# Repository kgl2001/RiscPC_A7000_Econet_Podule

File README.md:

# Introduction

This Econet Podule allows you to add Econet to your Acorn RISC PC or A7000.

The Podule has four main hardware sections:
  
* [Flash & Address Decoding](#flash--address-decoding)
* [Econet Module](#econet-module)
* Econet Clock
  - [WFF Implementation](#econet-clock---wff-implementation)
  - [Pico Implementation](#econet-clock---pico-implementation)
* [Termination](#onboard-termination)

By adding the Clock / Termination to the PCB, and by populating all four DIN5 sockets, the Acorn RISC PC or A7000 can act as an 'all in one' File Server solution when used along with Acorns Level 4 File Server software. No external clock, termination, or network infrastructure required. Just plug your client Econet enabled machine to one of the four DIN5 sockets on the rear of the board.

Some general notes about the different hardware sections, and RISC OS configuration, are provided below:

## Flash & Address Decoding
The Flash & Address Decoding hardware must be installed in all cases. Flash memory ICs SST39SF010, SST39SF020 or SST39SF040 (or equivalent) can be used with this module. Flash IC contents, `eco_flash` are included in a compressed .zip file within this repo. The unzipped `eco_flash` code should be written to the flash IC using a suitable programmer.

## Econet Module
The Podule PCB is provided with a 5 and 17 pin header, so you can plug in an ADF-10 or AEH-52 (or equivalent) module into the podule, instead of having to solder on all the Econet module components.

Econet Data Tx, Data Rx and Clock LEDs are present on the PCB. However, these will only work if you plan to add the other Econet components directly to the PCB. They won't work if you plan to use an ADF-10 or AEH-52 module.

If installing the Econet components directly onto the PCB, then one of the two channels of the line driver IC7 will be available for use by the onboard Econet clock circuit. If not installing the Econet clock circuit, it is still necessary to install resistor R31. This will disable the clock channel on the line driver, preventing it from interfering with any external clock.

## Econet Clock - WFF Implementation
The Econet clock is based on an original design by Simon Inns. Details can be found [here](https://www.waitingforfriday.com/?p=19).

The clock circuit has been modified slightly, so instead of driving the external hardware directly from the PIC, it is driven by the second channel on the Econet line driver that is otherwise spare.

If using an ADF-10 or AEH-52 module, instead of soldering the Econet parts directly onto the PCB, the second channel is unavailable to the Econet clock hardware. In this instance, if planning to install the onboard Econet clock circuit, it will be necessary to also install IC7 and resistor R25. The purpose of R25 is to disable the unused data channel on the line driver, preventing it from interfering with the network.

When the clock hardware is installed, channel 4 of DIP switch, SW1, can be used to enable or disable the clock hardware. When open circuit, the clock hardware is disabled. When short circuit, the clock hardware is enabled.

The PIC has two clock output signals that can be used to drive the external hardware directly, bypassing the clock channel of line driver IC7 completely. Jumper bank J6 can be used to connect the two clock signals from the PIC directly to external hardware. This is not a recommended configuration. However, if using these jumpers, then the clock channel of IC7 (if fitted) must be disabled.

Jumper JP5 is used to select which of the two clock output signals from the PIC is used to drive the clock channel of line driver IC7.

## Econet Clock - Pico Implementation
Provision has been made to connect a Pico based clock via a 2x20 pin header. This was primarily designed to accept a Pico board that was originally developed for other purposes. See [here](https://stardot.org.uk/forums/viewtopic.php?t=24932).

Like the WFF implementation, this solution also relies on the second channel of line driver IC7, so it needs to be fitted, along with R31, for this clock to work.

When this Pico clock module is plugged in, the second channel of line driver IC7 is enabled automatically (via Pico module Pin 20, which is tied to GND). It can only be disabled again by unplugging the Pico clock module. This would need to be done if using an external clock.

## Onboard Termination
An Econet network needs to be terminated to operate reliably. On larger networks this is typically done at the far ends of the network. Often, on these larger networks, an SJ Research clock is used. These clocks have a special circuit that allows special 'phantom powered' terminators to be used at the far ends. These special terminators are not compatible with the WFF clock or Pico clock used on this board. Instead, if using the onboard clock, then the onboard powered termination should be enabled. Jumper bank J3 is used to enable of disable the termination. Remove the jumpers to disable the termination.

## Configuring RISC OS
Please refer to [this](https://stardot.org.uk/forums/viewtopic.php?p=409582#p409582) post which provides guidance on configuring the RISC PC / A7000.

## Author

The RISC PC / A7000 Econet podule is developed and maintained by Ken Lowe.
    
## Hardware License (Creative Commons BY-SA 4.0)

Please see the following link for details: https://creativecommons.org/licenses/by-sa/4.0/

You are free to:

Share - copy and redistribute the material in any medium or format
Adapt - remix, transform, and build upon the material
for any purpose, even commercially.

This license is acceptable for Free Cultural Works.

The licensor cannot revoke these freedoms as long as you follow the license terms.

Under the following terms:

Attribution - You must give appropriate credit, provide a link to the license, and indicate if changes were made. You may do so in any reasonable manner, but not in any way that suggests the licensor endorses you or your use.

ShareAlike - If you remix, transform, or build upon the material, you must distribute your contributions under the same license as the original.

No additional restrictions - You may not apply legal terms or technological measures that legally restrict others from doing anything the license permits.

## Schematic and 3D Render
Econet Podule - Schematic:

Econet Podule - 3D Render:

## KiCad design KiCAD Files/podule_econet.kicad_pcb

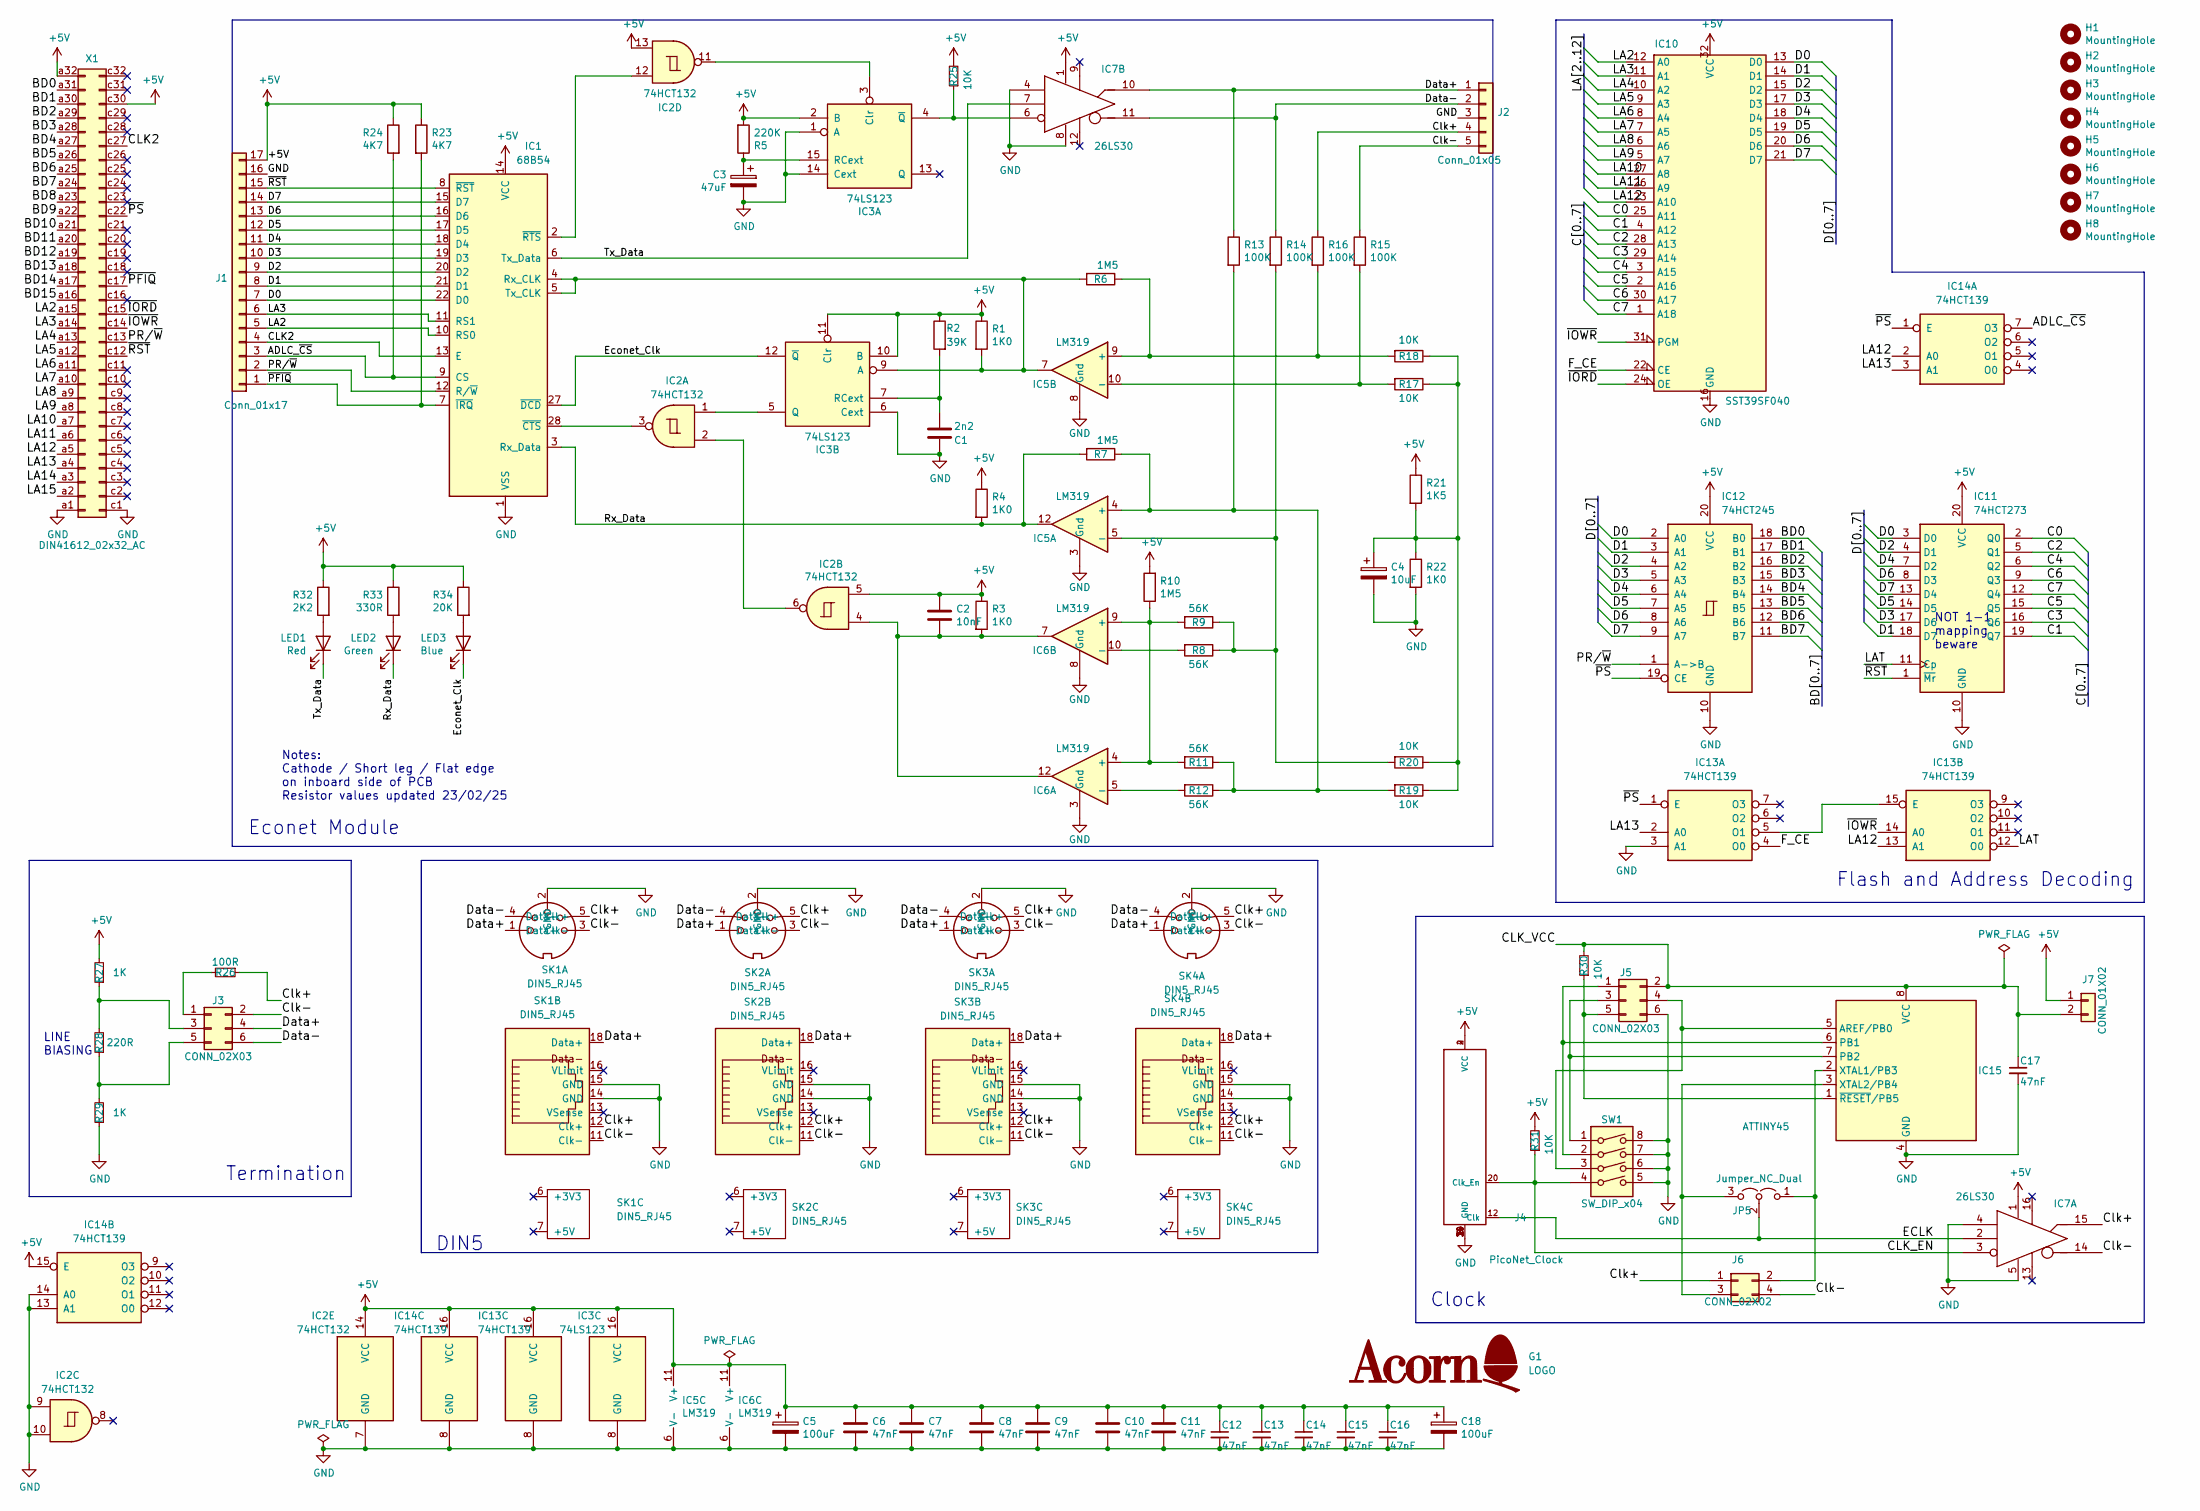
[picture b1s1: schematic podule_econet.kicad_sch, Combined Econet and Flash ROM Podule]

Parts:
C1: 2n2; C_Disc_D4.3mm_W1.9mm_P5.00_P2.54mm
C2: 10nF; C_Disc_D4.3mm_W1.9mm_P5.00_P2.54mm
C3: 47uF; CP_Radial_Tantal_D6.0mm_P2.50mm
C4: 10uF; CP_Radial_D5.0mm_P2.00mm
C5, C18: 100uF; CP_Radial_D5.0mm_P2.00mm
C6, C7, C8, C9, C10, C11, C12, C13, C14, C15, C16, C17: 47nF; C_Disc_D4.3mm_W1.9mm_P5.00mm
G1: LOGO; AcornLogo2
H1, H2, H3, H4, H7, H8: MountingHole; MountingHole_2.7mm
H5, H6: MountingHole; MountingHole_4mm
IC1: 68B54; DIP-28_W15.24mm
IC2: 74HCT132; DIP-14_W7.62mm
IC3: 74LS123; DIP-16_W7.62mm
IC5, IC6: LM319; DIP-14_W7.62mm
IC7: 26LS30; DIP-16_W7.62mm
IC10: SST39SF040; DIP-32_W15.24mm
IC11: 74HCT273; DIP-20_W7.62mm
IC12: 74HCT245; DIP-20_W7.62mm
IC13, IC14: 74HCT139; DIP-16_W7.62mm
IC15: ATTINY45; DIP-8_W7.62mm
J1: Conn_01x17; PinSocket_1x17_P2.54mm_Vertical
J2: Conn_01x05; PinSocket_1x05_P2.54mm_Vertical
J3, J5: CONN_02X03; PinHeader_2x03_P2.54mm_Vertical
J4: PicoNet_Clock; PicoNetClock
J6: CONN_02X02; PinHeader_2x02_P2.54mm_Vertical
J7: CONN_01X02; PinHeader_1x02_P2.54mm_Vertical
JP5: Jumper_NC_Dual; PinHeader_1x03_P2.54mm_Vertical
LED1: Red; LED_D3.0mm
LED2: Green; LED_D3.0mm
LED3: Blue; LED_D3.0mm
R1, R3, R4, R22: 1K0; R_Axial_DIN0207_L6.3mm_D2.5mm_P10.16mm_Horizontal
R2: 39K; R_Axial_DIN0207_L6.3mm_D2.5mm_P10.16mm_Horizontal
R5: 220K; R_Axial_DIN0207_L6.3mm_D2.5mm_P10.16mm_Horizontal
R6, R7, R10: 1M5; R_Axial_DIN0207_L6.3mm_D2.5mm_P10.16mm_Horizontal
R8, R9, R11, R12: 56K; R_Axial_DIN0207_L6.3mm_D2.5mm_P10.16mm_Horizontal
R13, R14, R15, R16: 100K; R_Axial_DIN0207_L6.3mm_D2.5mm_P10.16mm_Horizontal
R17, R18, R19, R20, R25, R30, R31: 10K; R_Axial_DIN0207_L6.3mm_D2.5mm_P10.16mm_Horizontal
R21: 1K5; R_Axial_DIN0207_L6.3mm_D2.5mm_P10.16mm_Horizontal
R23, R24: 4K7; R_Axial_DIN0207_L6.3mm_D2.5mm_P10.16mm_Horizontal
R26: 100R; R_Axial_DIN0207_L6.3mm_D2.5mm_P10.16mm_Horizontal
R27, R29: 1K; R_Axial_DIN0207_L6.3mm_D2.5mm_P10.16mm_Horizontal
R28: 220R; R_Axial_DIN0207_L6.3mm_D2.5mm_P10.16mm_Horizontal
R32: 2K2; R_Axial_DIN0207_L6.3mm_D2.5mm_P10.16mm_Horizontal
R33: 330R; R_Axial_DIN0207_L6.3mm_D2.5mm_P10.16mm_Horizontal
R34: 20K; R_Axial_DIN0207_L6.3mm_D2.5mm_P10.16mm_Horizontal
SK1, SK2, SK3, SK4: DIN5_RJ45; CombinedDIN5RJ45PinHeader90Deg
SW1: SW_DIP_x04; SW_DIP_SPSTx04_Slide_9.78x12.34mm_W7.62mm_P2.54mm
X1: DIN41612_02x32_AC; DIN41612_C_2x32_Male_Horizontal_THT

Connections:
+5V: C2.1, C5.1, C6.1, C7.1, C8.1, C9.1, C10.1, C11.1, C12.1, C13.1, C14.1, C15.1, C16.1, C18.1, IC1.14 (VCC), IC2.5, IC2.13, IC2.14 (VCC), IC3.2 (B), IC3.10 (B), IC3.11 (Clr), IC3.16 (VCC), IC5.11 (V+), IC6.11 (V+), IC7.1 (VCC), IC10.32 (VCC), IC11.20 (VCC), IC12.20 (VCC), IC13.16 (VCC), IC14.15 (E), IC14.16 (VCC), J1.17, J4.2 (VCC), J4.4 (VCC), J7.1, R1.1, R2.1, R3.1, R4.1, R5.2, R10.2, R21.1, R23.1, R24.1, R25.2, R27.2, R31.2, R32.1, R33.1, R34.1, X1.a32, X1.c30
/ADLC_~CS: IC1.9 (CS), IC14.7 (O3), J1.3, R24.2
/BD0: IC12.18 (B0), X1.a31
/BD1: IC12.17 (B1), X1.a30
/BD2: IC12.16 (B2), X1.a29
/BD3: IC12.15 (B3), X1.a28
/BD4: IC12.14 (B4), X1.a27
/BD5: IC12.13 (B5), X1.a26
/BD6: IC12.12 (B6), X1.a25
/BD7: IC12.11 (B7), X1.a24
/BD8: X1.a23
/BD9: X1.a22
/BD10: X1.a21
/BD11: X1.a20
/BD12: X1.a19
/BD13: X1.a18
/BD14: X1.a17
/BD15: X1.a16
/C0: IC10.25 (A11), IC11.2 (Q0)
/C1: IC10.4 (A12), IC11.19 (Q7)
/C2: IC10.28 (A13), IC11.5 (Q1)
/C3: IC10.29 (A14), IC11.16 (Q6)
/C4: IC10.3 (A15), IC11.6 (Q2)
/C5: IC10.2 (A16), IC11.15 (Q5)
/C6: IC10.30 (A17), IC11.9 (Q3)
/C7: IC10.1 (A18), IC11.12 (Q4)
/CLK2: IC1.13 (E), J1.4, X1.c27
/CLK_EN: IC7.3, J4.20 (Clk_En), R31.1, SW1.4
/CLK_VCC: C17.1, IC15.8 (VCC), J5.2, J7.2, R30.2
/Clk+: IC7.15 (OUT+), J2.4, J6.1, R16.1, R26.1, SK1.5 (Clk+), SK1.12 (Clk+), SK2.5 (Clk+), SK2.12 (Clk+), SK3.5 (Clk+), SK3.12 (Clk+), SK4.5 (Clk+), SK4.12 (Clk+)
/Clk-: IC7.14 (OUT-), J2.5, J3.2, J6.4, R15.1, SK1.3 (Clk-), SK1.11 (Clk-), SK2.3 (Clk-), SK2.11 (Clk-), SK3.3 (Clk-), SK3.11 (Clk-), SK4.3 (Clk-), SK4.11 (Clk-)
/D0: IC1.22 (D0), IC10.13 (D0), IC11.3 (D0), IC12.2 (A0), J1.7
/D1: IC1.21 (D1), IC10.14 (D1), IC11.18 (D7), IC12.3 (A1), J1.8
/D2: IC1.20 (D2), IC10.15 (D2), IC11.4 (D1), IC12.4 (A2), J1.9
/D3: IC1.19 (D3), IC10.17 (D3), IC11.17 (D6), IC12.5 (A3), J1.10
/D4: IC1.18 (D4), IC10.18 (D4), IC11.7 (D2), IC12.6 (A4), J1.11
/D5: IC1.17 (D5), IC10.19 (D5), IC11.14 (D5), IC12.7 (A5), J1.12
/D6: IC1.16 (D6), IC10.20 (D6), IC11.8 (D3), IC12.8 (A6), J1.13
/D7: IC1.15 (D7), IC10.21 (D7), IC11.13 (D4), IC12.9 (A7), J1.14
/Data+: IC7.10 (OUT+), J2.1, J3.4, R13.1, SK1.1 (Data+), SK1.18 (Data+), SK2.1 (Data+), SK2.18 (Data+), SK3.1 (Data+), SK3.18 (Data+), SK4.1 (Data+), SK4.18 (Data+)
/Data-: IC7.11 (OUT-), J2.2, J3.6, R14.1, SK1.4 (Data-), SK2.4 (Data-), SK3.4 (Data-), SK4.4 (Data-)
/ECLK: IC7.2 (Enable), J4.12 (Clk), JP5.2 (C)
/Econet_Clk: IC1.27 (~DCD), IC3.12 (~Q), LED3.1 (K)
/F_CE: IC10.22 (CE), IC13.4 (O0)
/LA2: IC1.10 (RS0), IC10.12 (A0), J1.5, X1.a15
/LA3: IC1.11 (RS1), IC10.11 (A1), J1.6, X1.a14
/LA4: IC10.10 (A2), X1.a13
/LA5: IC10.9 (A3), X1.a12
/LA6: IC10.8 (A4), X1.a11
/LA7: IC10.7 (A5), X1.a10
/LA8: IC10.6 (A6), X1.a9
/LA9: IC10.5 (A7), X1.a8
/LA10: IC10.27 (A8), X1.a7
/LA11: IC10.26 (A9), X1.a6
/LA12: IC10.23 (A10), IC13.13 (A1), IC14.2 (A0), X1.a5
/LA13: IC13.2 (A0), IC14.3 (A1), X1.a4
/LA14: X1.a3
/LA15: X1.a2
/LAT: IC11.11 (Cp), IC13.12 (O0)
/Rx_Data: IC1.3 (Rx_Data), IC5.12, LED2.1 (K), R4.2, R7.2
/Tx_Data: IC1.6 (Tx_Data), IC7.7 (Enable), LED1.1 (K)
/~IORD: IC10.24 (OE), X1.c15
/~IOWR: IC10.31 (PGM), IC13.14 (A0), X1.c14
/~PFIQ: IC1.7 (~IRQ), J1.1, R23.2, X1.c17
/~PS: IC12.19 (CE), IC13.1 (E), IC14.1 (E), X1.c22
/~RST: IC1.8 (~RST), IC11.1 (~Mr), J1.15, X1.c12
GND: C1.1, C3.2, C4.2, C5.2, C6.2, C7.2, C8.2, C9.2, C10.2, C11.2, C12.2, C13.2, C14.2, C15.2, C16.2, C17.2, C18.2, IC1.1 (VSS), IC2.7 (GND), IC2.9, IC2.10, IC3.1 (A), IC3.6 (Cext), IC3.8 (GND), IC3.14 (Cext), IC5.3 (Gnd), IC5.6 (V-), IC5.8 (Gnd), IC6.3 (Gnd), IC6.6 (V-), IC6.8 (Gnd), IC7.4 (Mode), IC7.5 (GND), IC7.8 (GND), IC10.16 (GND), IC11.10 (GND), IC12.10 (GND), IC13.3 (A1), IC13.8 (GND), IC14.8 (GND), IC14.13 (A1), IC14.14 (A0), IC15.4 (GND), J1.16, J2.3, J4.6 (GND), J4.9 (GND), J4.14 (GND), J4.25 (GND), J4.30 (GND), J4.34 (GND), J4.39 (GND), J5.6, R22.2, R29.1, SK1.2 (GND), SK1.14 (GND), SK1.15 (GND), SK2.2 (GND), SK2.14 (GND), SK2.15 (GND), SK3.2 (GND), SK3.14 (GND), SK3.15 (GND), SK4.2 (GND), SK4.14 (GND), SK4.15 (GND), SW1.5, SW1.6, SW1.7, SW1.8, X1.a1, X1.c1
unnamed: C2.2, IC2.4, IC6.7, IC6.12, R3.2
unnamed: C4.1, R17.1, R18.1, R19.1, R20.1, R21.2, R22.1
unnamed: IC1.4 (Rx_CLK), IC1.5 (Tx_CLK), IC3.9 (A), IC5.7, R1.2, R6.2
unnamed: IC1.28 (~CTS), IC2.3
unnamed: IC1.2 (~RTS), IC2.12
unnamed: IC2.2, IC2.6
unnamed: IC2.11, IC3.3 (Clr)
unnamed: C3.1, IC3.15 (RCext), R5.1
unnamed: IC3.4 (~Q), IC7.6, R25.1
unnamed: IC2.1, IC3.5 (Q)
unnamed: C1.2, IC3.7 (RCext), R2.2
unnamed: IC5.4 (+), R7.1, R11.1, R12.1, R13.2, R19.2
unnamed: IC5.5 (-), R8.1, R9.1, R14.2, R20.2
unnamed: IC5.9 (+), R6.1, R16.2, R18.2
unnamed: IC5.10 (-), R15.2, R17.2
unnamed: IC6.4 (+), IC6.9 (+), R9.2, R10.1, R11.2
unnamed: IC6.5 (-), R12.2
unnamed: IC6.10 (-), R8.2
unnamed: IC13.5 (O1), IC13.15 (E)
unnamed: IC15.5 (AREF/PB0), J5.4, SW1.3
unnamed: IC15.6 (PB1), J5.1, SW1.2
unnamed: IC15.7 (PB2), J5.3, SW1.1
unnamed: IC15.2 (XTAL1/PB3), J6.2, JP5.1 (A)
unnamed: IC15.3 (XTAL2/PB4), J6.3, JP5.3 (B)
unnamed: IC15.1 (~RESET/PB5), J5.5, R30.1
unnamed: J3.1, R26.2
unnamed: J3.3, R27.1, R28.2
unnamed: J3.5, R28.1, R29.2
unnamed: LED1.2 (A), R32.2
unnamed: LED2.2 (A), R33.2
unnamed: LED3.2 (A), R34.2

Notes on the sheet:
Clock
Termination
NOT 1-1 mapping beware
LINE BIASING
DIN5
Flash and Address Decoding
Econet Module
Notes: Cathode / Short leg / Flat edge on inboard side of PCB Resistor values updated 23/02/25

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
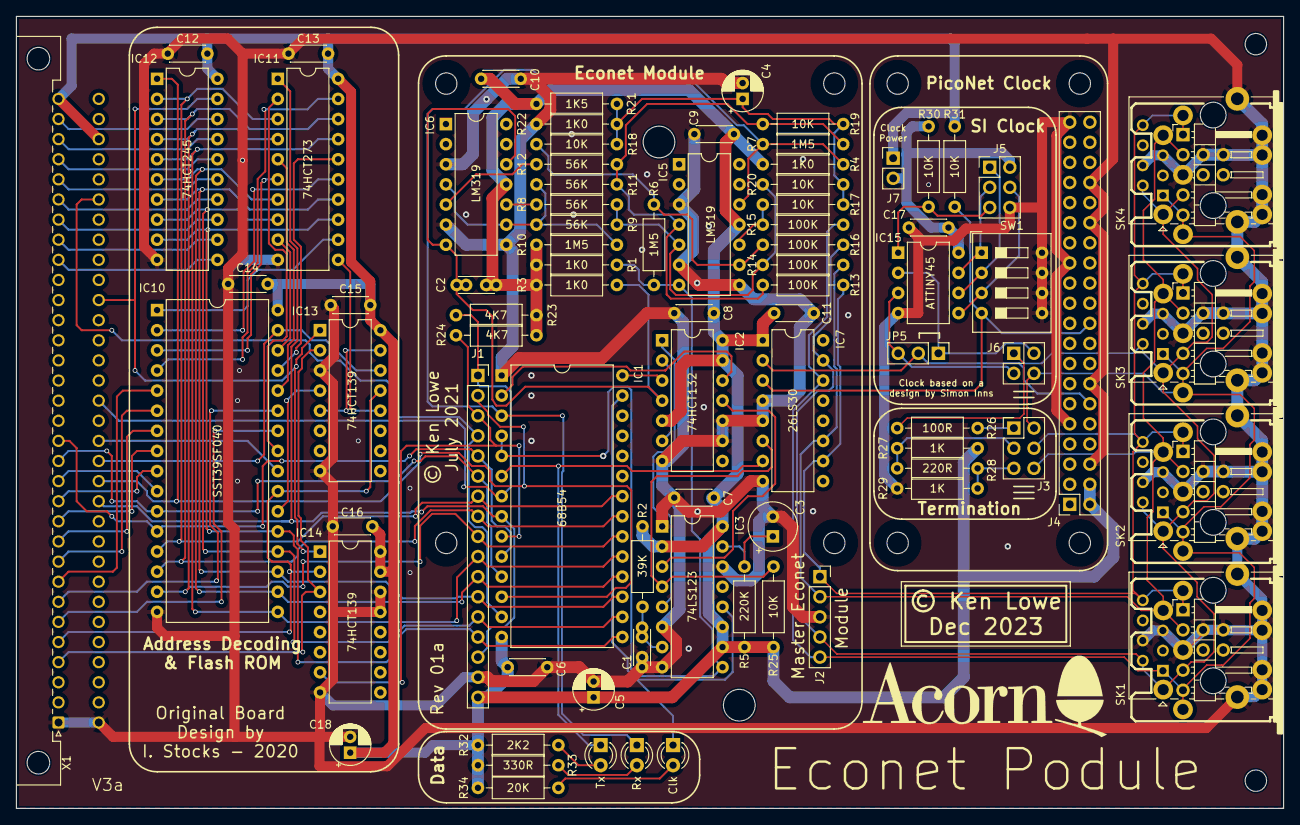
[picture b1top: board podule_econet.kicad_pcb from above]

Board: 2 copper layers, 160.0 x 100.0 mm, 90 parts (0 on the bottom side), 89 nets.

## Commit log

2024-05-24 Create README.md
    Added Schematic and 3D render
2025-10-14 Add 3D model for backplate
2025-10-14 Upload Backplate KiCAD files
2025-10-14 Add Acorn silkscreen logo
2025-10-14 Updated for KiCAD V9
    + Updated 3D model file locations
2025-10-14 Updated schematic PDF
2025-10-14 Updated 3D models
2025-10-15 Remove JLC serial mark from PCB
    Add 8x8mm box to rear of PCB for JLC 2D serial code instead.
2025-10-27 fix links

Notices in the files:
KiCAD Files/podule_econet.kicad_pcb:
© Ken Lowe
